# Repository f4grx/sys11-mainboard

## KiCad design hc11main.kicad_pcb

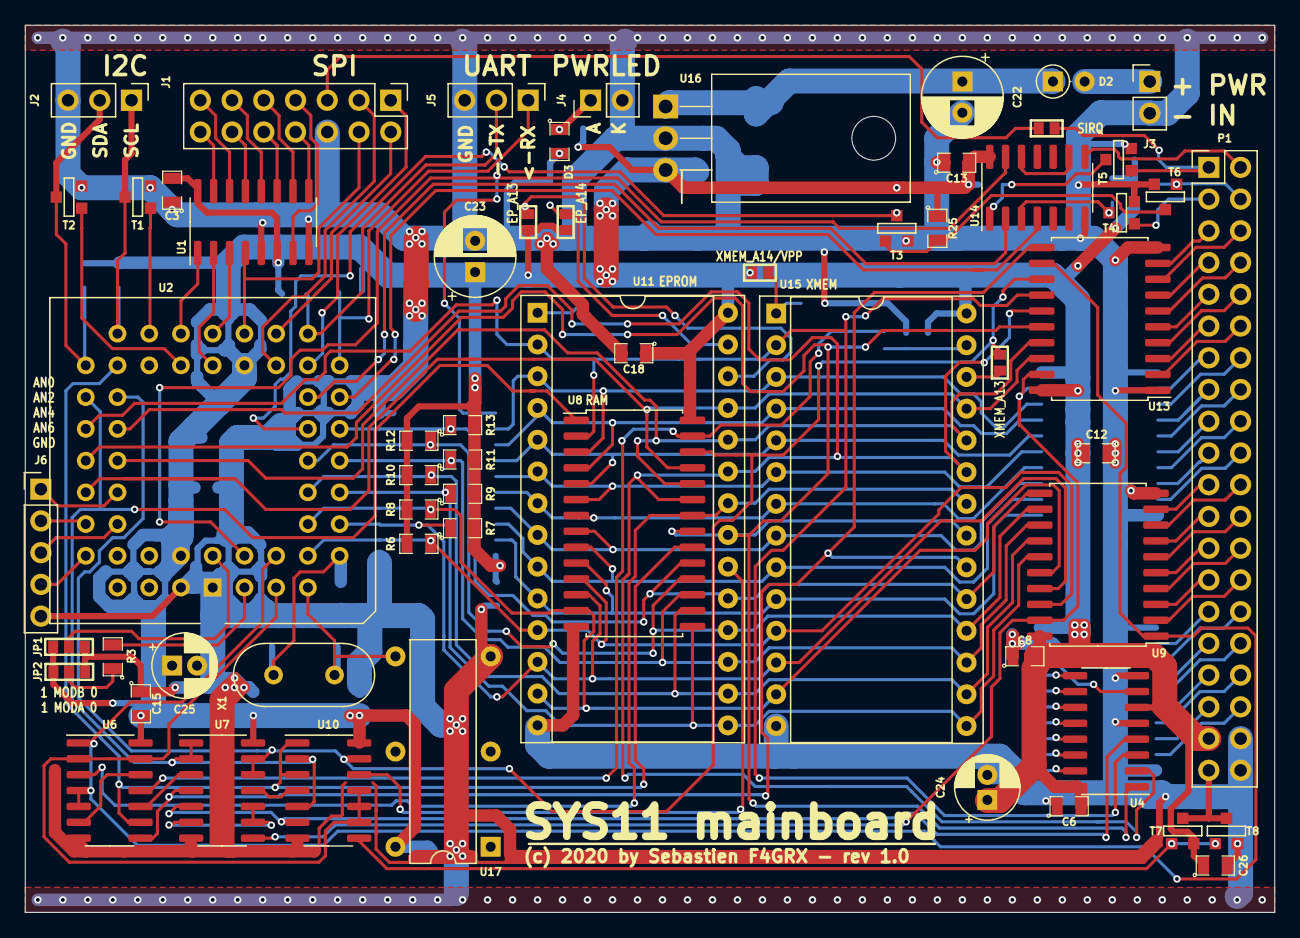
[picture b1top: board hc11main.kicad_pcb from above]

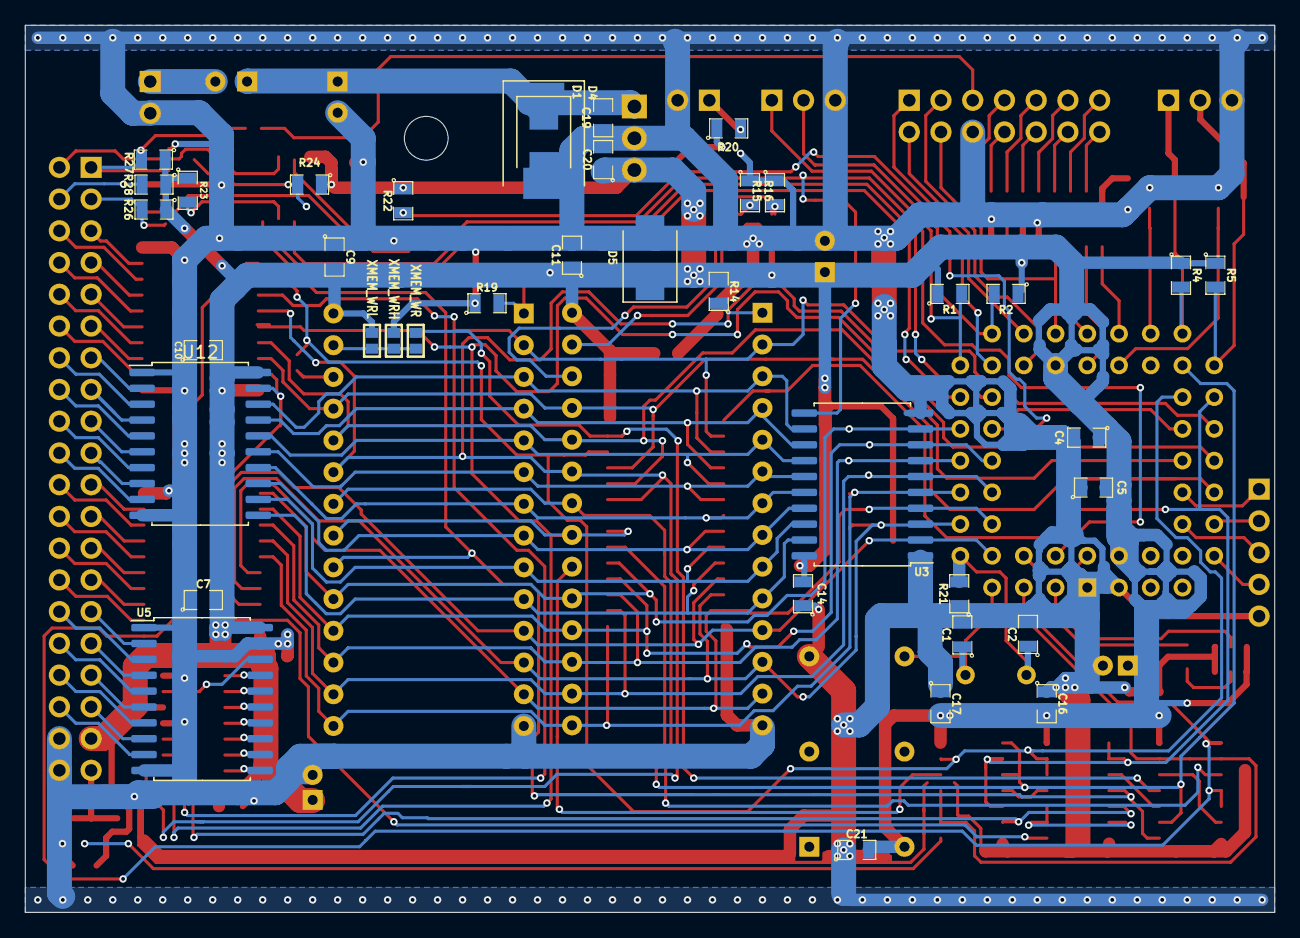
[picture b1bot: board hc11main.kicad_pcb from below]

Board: 2 copper layers, 100.0 x 71.0 mm, 100 parts (39 on the bottom side), 132 nets.

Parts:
C1, C2: CSMALL; 0805_m2012
C3, C6, C7, C8, C9, C10, C12, C13, C14, C15, C16, C17, C19, C20, C21, C26: 100n; 0805_m2012
C4: 10n; 0805_m2012
C5: 1u; 0805_m2012
C11, C18: 1uF; 0805_m2012
C22, C23: 100u; CP_Radial_D6.3mm_P2.50mm
C24, C25: 47u; CP_Radial_D5.0mm_P2.00mm
D1: SMBJ15A; D_SMB
D2: Schottky; D_DO-35_SOD27_P2.54mm_Vertical_AnodeUp
D3: LED; 0805_m2012
D4: SMCJ15A; D_SMC
D5: SMBJ5A; D_SMB
J1: SPI; PinHeader_2x07_P2.54mm_Vertical
J2: CONN_I2C; PinHeader_1x03_P2.54mm_Vertical
J3: CONN_PWR; PinHeader_1x02_P2.54mm_Vertical
J4: CONN_LED; PinHeader_1x02_P2.54mm_Vertical
J5: CONN_UART; PinHeader_1x03_P2.54mm_Vertical
J6: Conn_01x05; PinHeader_1x05_P2.54mm_Vertical
JP1, JP2: Jumper3; SMDPADS_3
JP3: XMEM_A13; SMDPADS_2
JP4: XMEM_WR; SMDPADS_2
JP5: EP_A14; SMDPADS_2
JP6: EP_A13; SMDPADS_2
JP7: XMEM_A14/VPP; SMDPADS_2
JP8: XMEM_WRL; SMDPADS_2
JP9: XMEM_WRH; SMDPADS_2
JP10: SIRQ; SMDPADS_2
P1: CONN_2X20; PinHeader_2x20_P2.54mm_Vertical
R1, R2, R3, R6, R7, R8, R9, R10, R11, R12, R13, R21, R22, R23, R24, R25, R26, R27, R28: 10k; 0805_m2012
R4, R5: 4k7; 0805_m2012
R14: 1k; 0805_m2012
R15, R16, R19: 100k; 0805_m2012
R20: RSMALL; 0805_m2012
T1, T2: BS170/2N7000 (SOT23); SOT23GDS
T3, T4, T5, T6: BS170; SOT23GDS
T7: BS250 (SOT23); SOT23GDS
T8: BS170 (SOT23); SOT23GDS
U1, U4: 74LS138; SOIC-16_3.9x9.9mm_P1.27mm
U2: 68HC11A0_PLCC; PLCC-52_THT-Socket
U3: 74LS573; SOIC-20W_7.5x12.8mm_P1.27mm
U5, U9, U12, U13: 74LS245; SOIC-20W_7.5x12.8mm_P1.27mm
U6, U7: 74LS00; SOIC-14_3.9x8.7mm_P1.27mm
U8: 62256; SOIC-28W_7.5x17.9mm_P1.27mm
U10: 74LS10; SOIC-14_3.9x8.7mm_P1.27mm
U11: 27256; DIP-28_W15.24mm_Socket
U14: 74HCT04; SOIC-14_3.9x8.7mm_P1.27mm
U15: 62256; DIP-28_W15.24mm_Socket
U16: 7805; TO-220-3_Horizontal_TabDown
U17: OSC_DIL14; DIP-OSCILLATOR
X1: 8 MHz; Crystal_HC49-U_Vertical

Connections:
/A0: U3.19, U8.10, U11.10, U12.11, U15.10
/A1: U3.18, U8.9, U11.9, U12.12, U15.9
/A2: U3.17, U8.8, U11.8, U12.13, U15.8
/A3: U3.16, U8.7, U11.7, U12.14, U15.7
/A4: U3.15, U8.6, U11.6, U12.15, U15.6
/A5: U3.14, U8.5, U11.5, U12.16, U15.5
/A6: U3.13, U8.4, U11.4, U12.17, U15.4
/A7: U3.12, U8.3, U11.3, U12.18, U15.3
/A8: U2.42, U8.25, U11.25, U13.18, U15.25
/A9: U2.41, U8.24, U11.24, U13.17, U15.24
/A10: U2.40, U4.1, U8.21, U11.21, U13.16, U15.21
/A11: U2.39, U4.2, U8.23, U11.23, U13.15, U15.23
/A12: U2.38, U4.3, U8.2, U11.2, U13.14, U15.2
/A13: JP3.2, U2.37, U7.12, U7.13, U8.26, U10.13, U13.13
/A14: U2.36, U7.1, U7.2, U8.1, U10.2, U10.5
/A15: U2.35, U6.9, U8.20, U10.1, U10.3
/AN0: J6.1, U2.43
/AN2: J6.2, U2.44
/AN4: J6.3, U2.45
/AN6: J6.4, U2.46
/AS: U2.4, U3.11, U14.13
/CPURST: R25.2, T3.G, T6.D
/CSEN: J1.4, U1.4, U2.25
/D0: R6.1, U2.9, U3.2, U8.11, U9.18, U11.11, U15.11
/D1: R7.1, U2.10, U3.3, U8.12, U9.17, U11.12, U15.12
/D2: R8.1, U2.11, U3.4, U8.13, U9.16, U11.13, U15.13
/D3: R9.1, U2.12, U3.5, U8.15, U9.15, U11.15, U15.15
/D4: R10.1, U2.13, U3.6, U8.16, U9.14, U11.16, U15.16
/D5: R11.1, U2.14, U3.7, U8.17, U9.13, U11.17, U15.17
/D6: R12.1, U2.15, U3.8, U8.18, U9.12, U11.18, U15.18
/D7: R13.1, U2.16, U3.9, U8.19, U9.11, U11.19, U15.19
/E: U2.5, U6.2, U6.13, U10.9, U10.10, U10.11
/EP_A13: JP6.1, R15.2, U11.26
/EP_A14: JP5.1, R16.2, U11.27
/EXTAL: C1.1, U2.7, U17.8, X1.1
/IRQ: R24.2, T5.D, U14.1
/LED: D3.1, J4.1, R20.2
/MISO: J1.1, U2.22
/MODA: R3.2, U2.3
/MODB: JP1.2, U2.2
/MOSI: J1.2, U2.23
/PWR: D2.2, J3.1
/RXIN: J5.1, R1.2, U2.20
/R~W: U2.6, U6.1, U6.4, U6.5, U9.1, U13.12
/S0: U4.15, U5.11
/S1: U4.14, U5.12
/S2: U4.13, U5.13
/S3: U4.12, U5.14
/S4: U4.11, U5.15
/S5: U4.10, U5.16
/S6: U4.9, U5.17
/S7: U4.7, U5.18
/SCL: J2.1, R4.2, T1.D, U2.33
/SCLK: J1.3, U2.24
/SDA: J2.2, R5.2, T2.D, U2.34
/SIRQ: J1.5, JP10.2
/SPIA0: U1.1, U2.29
/SPIA1: U1.2, U2.28
/SPIA2: U1.3, U2.27
/SPICS0: J1.14, U1.15
/SPICS1: J1.13, U1.14
/SPICS2: J1.12, U1.13
/SPICS3: J1.11, U1.12
/SPICS4: J1.10, U1.11
/SPICS5: J1.9, U1.10
/SPICS6: J1.8, U1.9
/SPICS7: J1.7, U1.7
/TXOUT: J5.2, R2.2, U2.21
/VIN: C19.1, C22.1, D1.1, D2.1, D4.1, U16.1
/XIRQ: R23.2, T4.D, U14.3
/XTAL: C2.1, R21.2, U2.8, X1.2
/bA0: P1.20, U12.9
/bA1: P1.19, U12.8
/bA2: P1.18, U12.7
/bA3: P1.17, U12.6
/bA4: P1.16, U12.5
/bA5: P1.15, U12.4
/bA6: P1.14, U12.3
/bA7: P1.13, U12.2
/bA8: P1.12, U13.2
/bA9: P1.11, U13.3
/bA10: P1.10, U13.4
/bA11: P1.9, U13.5
/bA12: P1.8, U13.6
/bA13: P1.7, U13.7
/bAS: P1.2, U14.8
/bD0: P1.28, U9.2
/bD1: P1.27, U9.3
/bD2: P1.26, U9.4
/bD3: P1.25, U9.5
/bD4: P1.24, U9.6
/bD5: P1.23, U9.7
/bD6: P1.22, U9.8
/bD7: P1.21, U9.9
/bE: P1.39, T7.D, T8.D
/bR~W: P1.6, U13.8
/bS0: P1.36, U5.9
/bS1: P1.35, U5.8
/bS2: P1.34, U5.7
/bS3: P1.33, U5.6
/bS4: P1.32, U5.5
/bS5: P1.31, U5.4
/bS6: P1.30, U5.3
/bS7: P1.29, U5.2
/b~CSXRAM: P1.5, U13.9
/b~IRQ: JP10.1, P1.1, R27.2, T5.G
/b~RST: P1.4, R28.2, T6.G
/b~XIRQ: P1.3, R26.2, T4.G
/drSCL: T1.G, U2.31
/drSDA: T2.G, U2.30
/~A13: U7.11, U10.4
/~A14: U6.10, U7.3
/~AS: U14.9, U14.12
/~CPURST: R22.2, T3.D, U2.17
/~CSEXT: U7.8, U9.19, U12.19, U13.19
/~CSIO: U4.4, U7.5, U10.6
/~CSROM: U10.12, U11.20
/~CSXRAM: U6.8, U7.4, U13.11, U15.20
/~E: T7.G, T8.G, U10.8
/~IRQ: U2.19, U14.2
/~RD: U6.3, U8.22, U11.22, U15.22
/~WR: JP4.2, U6.11, U8.27
/~XIRQ: U2.18, U14.4
GND: C1.2, C2.2, C3.1, C4.2, C5.1, C6.1, C7.1, C8.1, C9.1, C10.1, C11.2, C12.1, C13.1, C14.1, C15.1, C16.1, C17.1, C18.2, C19.2, C20.2, C21.1, C22.2, C23.2, C24.2, C25.2, C26.2, D1.2, D3.2, D4.2, D5.2, J1.6, J2.3, J3.2, J4.2, J5.3, J6.5, JP1.3, JP2.3, JP9.2, P1.38, P1.40, R15.1, R16.1, R19.1, R21.1, T1.S, T2.S, T3.S, T4.S, T5.S, T6.S, T8.S, U1.5, U1.8, U2.1, U2.51, U3.1, U3.10, U4.5, U4.8, U5.1, U5.10, U5.19, U6.7, U7.7, U8.14, U9.10, U10.7, U11.14, U12.1, U12.10, U13.1, U13.10, U14.7, U15.14, U16.2, U17.7
unnamed: JP2.2, R3.1
unnamed: JP3.1, U15.26
unnamed: JP4.1, JP8.1, JP9.1, U15.27
unnamed: JP7.1, R19.2, U15.1
unnamed: R14.1, U11.1
unnamed: U6.6, U6.12
unnamed: U7.6, U7.9, U7.10
VCC: C3.2, C4.1, C5.2, C6.2, C7.2, C8.2, C9.2, C10.2, C11.1, C12.2, C13.2, C14.2, C15.2, C16.2, C17.2, C18.1, C20.1, C21.2, C23.1, C24.1, C25.1, C26.1, D5.1, JP1.1, JP2.1, JP5.2, JP6.2, JP7.2, JP8.2, P1.37, R1.1, R2.1, R4.1, R5.1, R6.2, R7.2, R8.2, R9.2, R10.2, R11.2, R12.2, R13.2, R14.2, R20.1, R22.1, R23.1, R24.1, R25.1, R26.1, R27.1, R28.1, T7.S, U1.6, U1.16, U2.26, U2.52, U3.20, U4.6, U4.16, U5.20, U6.14, U7.14, U8.28, U9.20, U10.14, U11.28, U12.20, U13.20, U14.14, U15.28, U16.3, U17.14

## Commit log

2020-01-09 more hardware around
2020-01-13 add design for a keyboard
2020-06-10 main board: continue routing
2020-06-26 almost completed routing
2020-07-06 finish routing everything, optimize routing, fix 2 missing CS traces
2020-07-06 update some labels
2020-07-16 board optimizations

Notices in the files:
hc11main.kicad_pcb:
(c) 2020 by Sebastien F4GRX - rev 1.0
